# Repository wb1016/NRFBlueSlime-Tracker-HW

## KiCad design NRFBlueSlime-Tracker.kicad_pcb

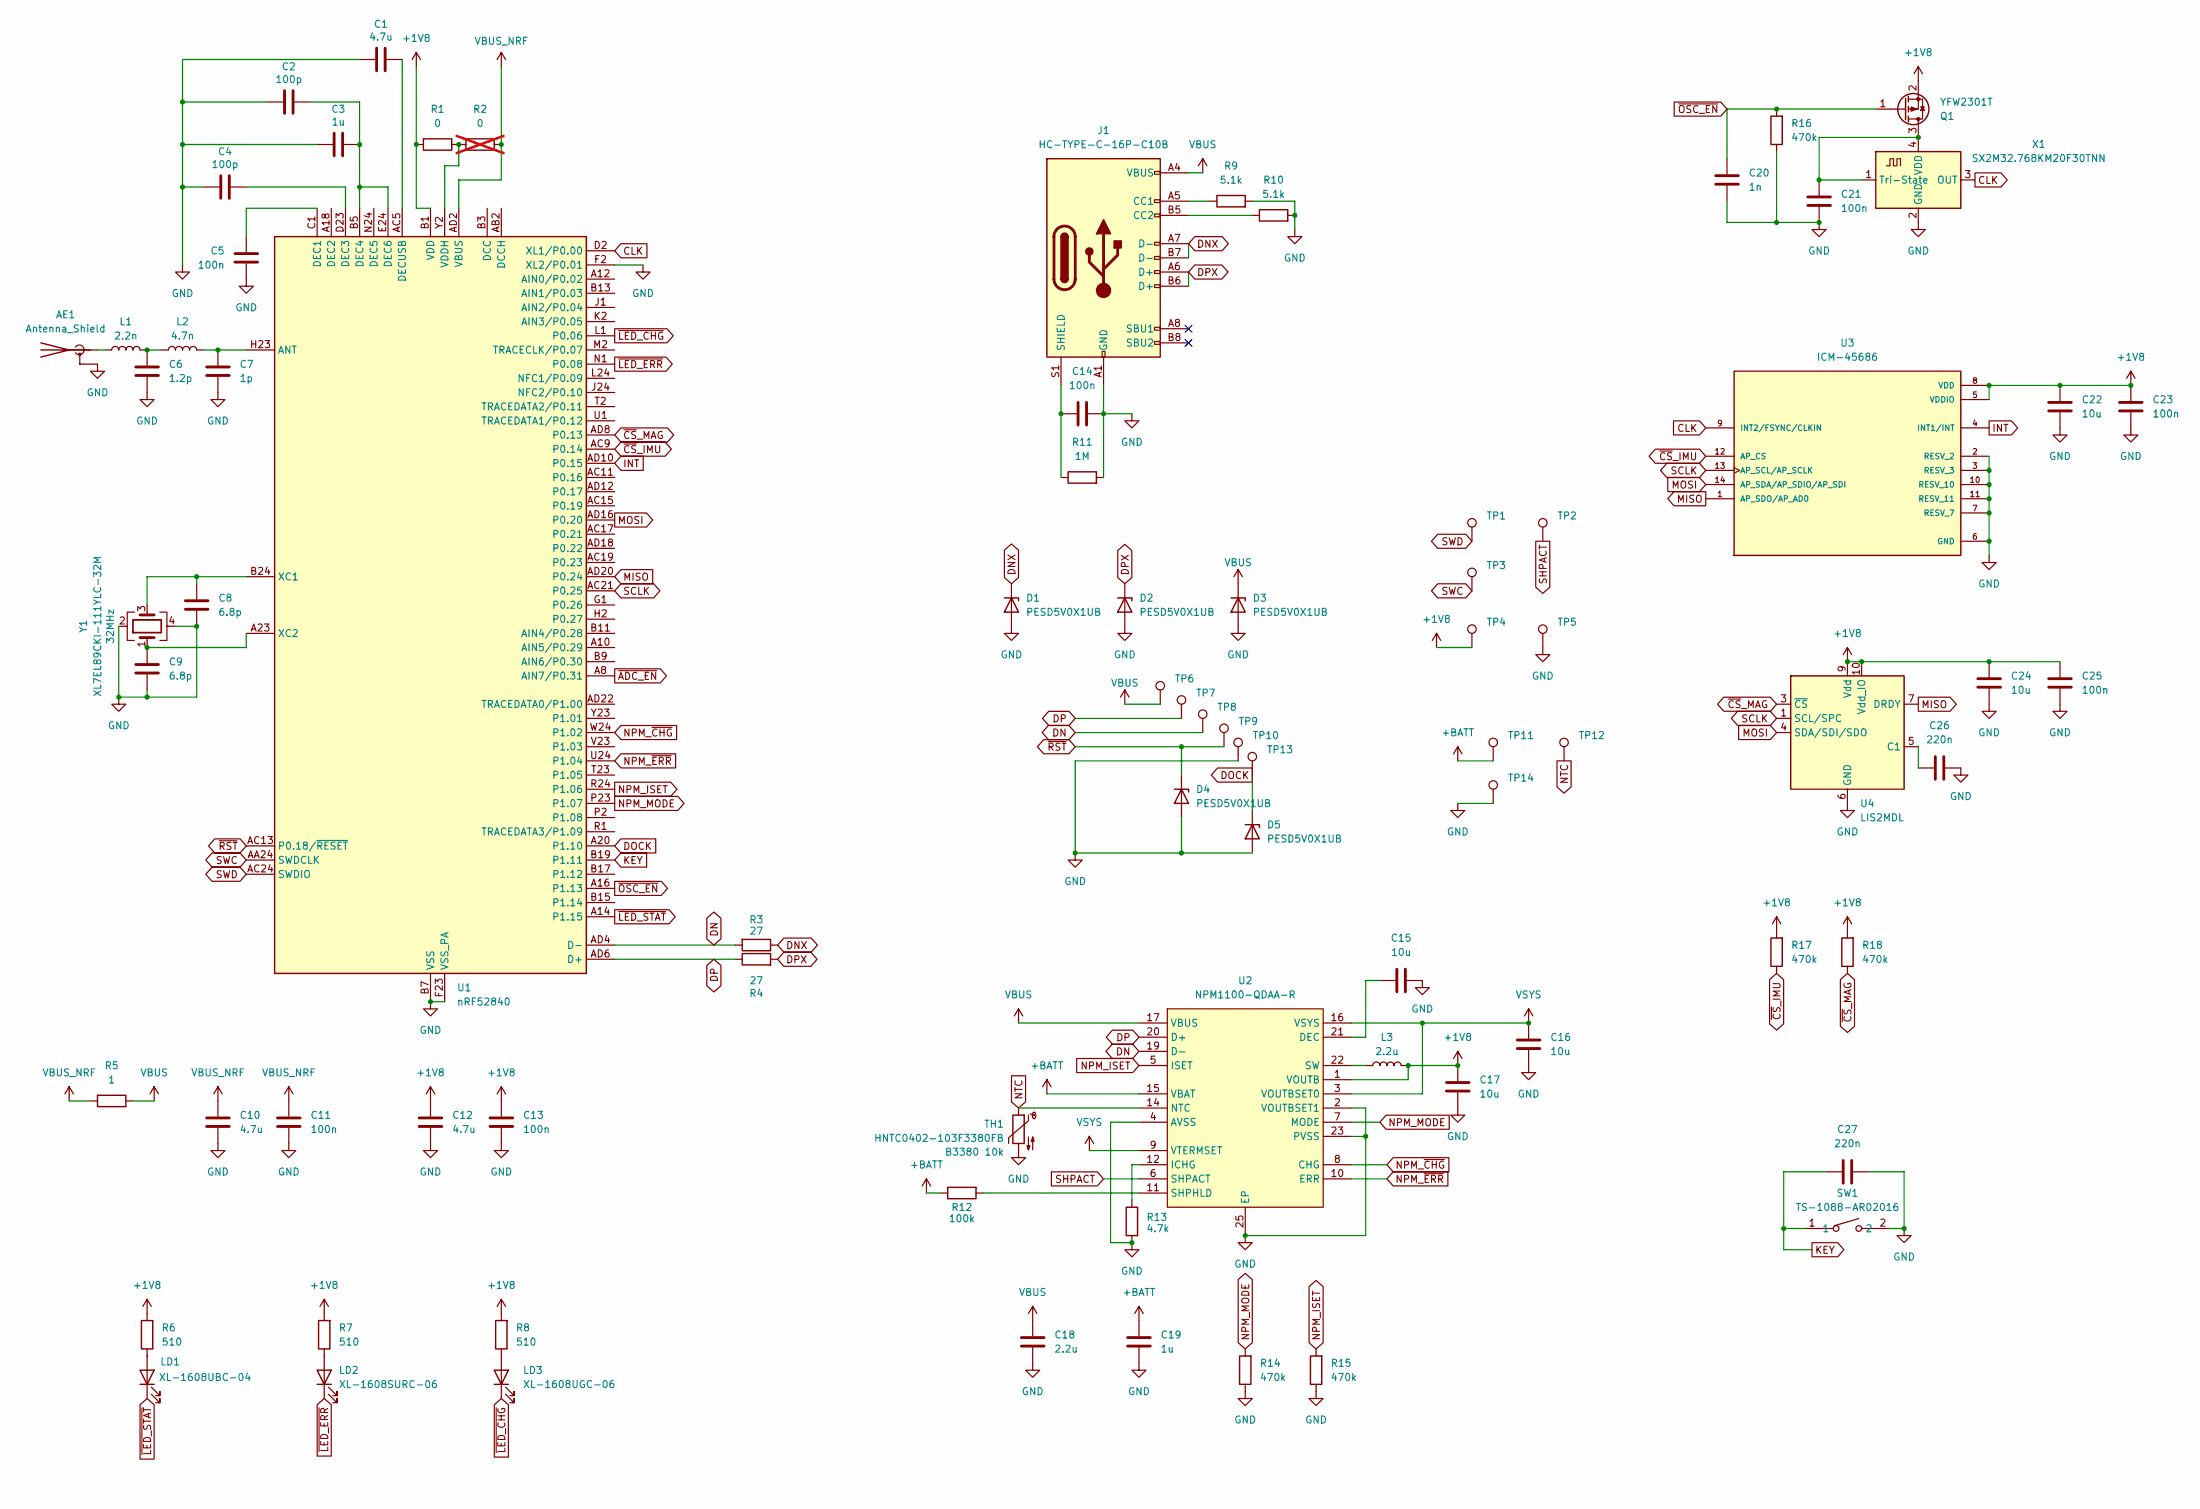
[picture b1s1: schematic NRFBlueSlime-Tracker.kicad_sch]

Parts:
AE1: Antenna_Shield; MIFA_BLE_ANT
C1, C10, C12: 4.7u; C_0603_1608Metric
C2, C4: 100p; C_0402_1005Metric
C3, C19: 1u; C_0603_1608Metric
C5, C11, C13, C14, C21, C23, C25: 100n; C_0402_1005Metric
C6: 1.2p; C_0402_1005Metric
C7: 1p; C_0402_1005Metric
C8, C9: 6.8p; C_0402_1005Metric
C15, C16, C17, C22, C24: 10u; C_0603_1608Metric
C18: 2.2u; C_0603_1608Metric
C20: 1n; C_0402_1005Metric
C26, C27: 220n; C_0402_1005Metric
D1, D2, D3, D4, D5: PESD5V0X1UB; D_SOD-882
J1: HC-TYPE-C-16P-C10B; USB-C-SMD_HC-TYPE-C-16P-C10B
L1: 2.2n; L_0402_1005Metric
L2: 4.7n; L_0402_1005Metric
L3: 2.2u; L_1210_3225Metric
LD1: XL-1608UBC-04; LED_0603_1608Metric
LD2: XL-1608SURC-06; LED_0603_1608Metric
LD3: XL-1608UGC-06; LED_0603_1608Metric
Q1: YFW2301T; SOT-523
R1: 0; R_0603_1608Metric
R2: 0; R_0603_1608Metric; not fitted
R3, R4: 27; R_0402_1005Metric
R5: 1; R_0603_1608Metric
R6, R7, R8: 510; R_0402_1005Metric
R9, R10: 5.1k; R_0402_1005Metric
R11: 1M; R_0402_1005Metric
R12: 100k; R_0402_1005Metric
R13: 4.7k; R_0402_1005Metric
R14, R15, R16, R17, R18: 470k; R_0402_1005Metric
SW1: TS-1088-AR02016; SW-SMD_L3.9-W3.0-P4.45; LCSC Part C720477
TH1: HNTC0402-103F3380FB; R_0402_1005Metric
TP1, TP2, TP3, TP4, TP5, TP6, TP7, TP8, TP9, TP10, TP11, TP12, TP13, TP14: TestPoint; TestPoint_Pad_1.0x1.0mm
U1: nRF52840; Nordic_AQFN-73-1EP_7x7mm_P0.5mm
U2: NPM1100-QDAA-R; QFN50P400X400X90-25N-D; Mouser Part Number 949-NPM1100-QDAA-R
U3: ICM-45686; PQFN50P300X250X97-14N; PARTREV 1.2
U4: LIS2MDL; LGA-12_2x2mm_P0.5mm
X1: SX2M32.768KM20F30TNN; Crystal_SMD_2520-4Pin_2.5x2.0mm; LCSC Part C387463
Y1: XL7EL89CKI-111YLC-32M; Crystal_SMD_2016-4Pin_2.0x1.6mm

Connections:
+1V8: C12.1, C13.1, C17.1, C22.1, C23.1, C24.1, C25.1, L3.2, Q1.2 (S), R1.2, R6.2, R7.2, R8.2, R17.2, R18.2, TP4.1, U1.A22 (VDD), U1.AD14 (VDD), U1.AD23 (VDD), U1.B1 (VDD), U1.W1 (VDD), U2.1 (VOUTB), U3.5 (VDDIO), U3.8 (VDD), U4.9 (Vdd), U4.10 (Vdd_IO)
+BATT: C19.2, R12.1, TP11.1, U2.15 (VBAT)
CLK: U1.D2 (XL1/P0.00), U3.9 (INT2/FSYNC/CLKIN), X1.3 (OUT)
DN: R3.2, TP8.1, U1.AD4 (D-), U2.19 (D-)
DNX: D1.1 (K), J1.A7 (D-), J1.B7 (D-), R3.1
DOCK: D5.1 (K), TP13.1, U1.A20 (P1.10)
DP: R4.1, TP7.1, U1.AD6 (D+), U2.20 (D+)
DPX: D2.1 (K), J1.A6 (D+), J1.B6 (D+), R4.2
GND: AE1.2 (Shield), C1.1, C2.1, C3.1, C4.1, C5.1, C6.1, C7.1, C8.1, C9.1, C10.2, C11.2, C12.2, C13.2, C14.2, C15.1, C16.1, C17.2, C18.1, C19.1, C20.2, C21.2, C22.2, C23.2, C24.2, C25.2, C26.2, C27.2, D1.2 (A), D2.2 (A), D3.2 (A), D4.2 (A), D5.2 (A), J1.A1 (GND), J1.A12 (GND), J1.B1 (GND), J1.B12 (GND), R9.2, R10.2, R11.2, R13.2, R14.1, R15.1, R16.1, SW1.2, TH1.2, TP5.1, TP10.1, TP14.1, U1.B7 (VSS), U1.EP (VSS), U1.F2 (XL2/P0.01), U1.F23 (VSS_PA), U2.2 (VOUTBSET1), U2.4 (AVSS), U2.23 (PVSS), U2.25 (EP), U3.2 (RESV_2), U3.3 (RESV_3), U3.6 (GND), U3.7 (RESV_7), U3.10 (RESV_10), U3.11 (RESV_11), U4.6 (GND), U4.8 (GND), X1.2 (GND), Y1.2, Y1.4
INT: U1.AD10 (P0.15), U3.4 (INT1/INT)
KEY: C27.1, SW1.1, U1.B19 (P1.11)
MISO: U1.AD20 (P0.24), U3.1 (AP_SDO/AP_AD0), U4.7 (DRDY)
MOSI: U1.AD16 (P0.20), U3.14 (AP_SDA/AP_SDIO/AP_SDI), U4.4 (SDA/SDI/SDO)
NPM_ISET: R15.2, U1.R24 (P1.06), U2.5 (ISET)
NPM_MODE: R14.2, U1.P23 (P1.07), U2.7 (MODE)
NPM_~CHG: U1.W24 (P1.02), U2.8 (CHG)
NPM_~ERR: U1.U24 (P1.04), U2.10 (ERR)
NTC: TH1.1, TP12.1, U2.14 (NTC)
unnamed: AE1.1 (A), L1.1
unnamed: C6.2, L1.2, L2.1
unnamed: J1.A5 (CC1), R9.1
unnamed: J1.B5 (CC2), R10.1
unnamed: C14.1, J1.S1 (SHIELD), R11.1
unnamed: LD1.2 (A), R6.1
unnamed: LD2.2 (A), R7.1
unnamed: LD3.2 (A), R8.1
unnamed: C21.1, Q1.3 (D), X1.1 (Tri-State), X1.4 (VDD)
unnamed: C7.2, L2.2, U1.H23 (ANT)
unnamed: C5.2, U1.C1 (DEC1)
unnamed: C4.2, U1.D23 (DEC3)
unnamed: C2.2, C3.2, U1.B5 (DEC4), U1.E24 (DEC6)
unnamed: C1.2, U1.AC5 (DECUSB)
unnamed: R1.1, R2.2, U1.Y2 (VDDH)
unnamed: C8.2, U1.B24 (XC1), Y1.3
unnamed: C9.2, U1.A23 (XC2), Y1.1
unnamed: C15.2, U2.21 (DEC)
unnamed: R13.1, U2.12 (ICHG)
unnamed: R12.2, U2.11 (SHPHLD)
unnamed: L3.1, U2.22 (SW)
unnamed: C26.1, U4.5 (C1)
SCLK: U1.AC21 (P0.25), U3.13 (AP_SCL/AP_SCLK), U4.1 (SCL/SPC)
SHPACT: TP2.1, U2.6 (SHPACT)
SWC: TP3.1, U1.AA24 (SWDCLK)
SWD: TP1.1, U1.AC24 (SWDIO)
VBUS: C18.2, D3.1 (K), J1.A4 (VBUS), J1.A9 (VBUS), J1.B4 (VBUS), J1.B9 (VBUS), R5.1, TP6.1, U2.17 (VBUS)
VBUS_NRF: C10.1, C11.1, R2.1, R5.2, U1.AD2 (VBUS)
VSYS: C16.2, U2.3 (VOUTBSET0), U2.9 (VTERMSET), U2.16 (VSYS)
~ADC_EN: U1.A8 (AIN7/P0.31)
~CS_IMU: R17.1, U1.AC9 (P0.14), U3.12 (AP_CS)
~CS_MAG: R18.1, U1.AD8 (P0.13), U4.3 (~CS)
~LED_CHG: LD3.1 (K), U1.L1 (P0.06)
~LED_ERR: LD2.1 (K), U1.N1 (P0.08)
~LED_STAT: LD1.1 (K), U1.A14 (P1.15)
~OSC_EN: C20.1, Q1.1 (G), R16.2, U1.A16 (P1.13)
~RST: D4.1 (K), TP9.1, U1.AC13 (P0.18/~RESET)

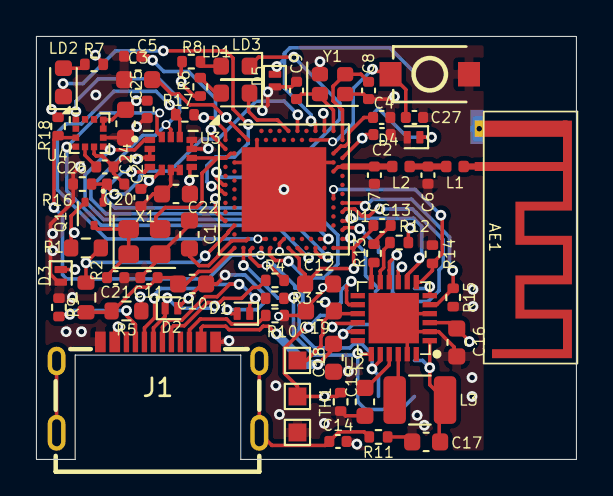
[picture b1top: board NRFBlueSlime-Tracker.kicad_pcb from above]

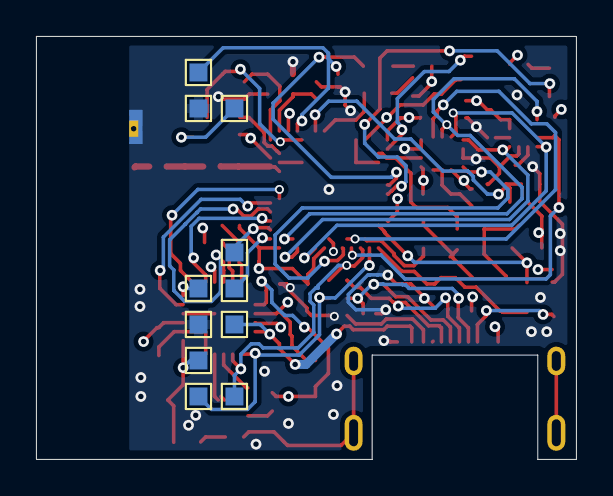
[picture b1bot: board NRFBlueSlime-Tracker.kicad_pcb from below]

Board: 4 copper layers, 30.0 x 23.5 mm, 81 parts (11 on the bottom side), 54 nets.

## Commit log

2024-04-18 asdfadsfda
2024-04-26 dhshdfsdgjfhfghj
2024-06-04 asdfa
2024-07-02 nrf52832 rev
2024-07-03 use metric spacing for dock, route switch
2024-07-28 mdbt42
2024-09-11 done nrf52840 ver
2024-09-12 hide ref, draw dimension mark
2024-09-12 fix offset sw1, upload 3d
2024-09-12 fix gnd testpad
2024-09-12 add case
2024-09-12 use copper fill in in1cu layer
2024-09-12 Label TP
2024-10-05 new ver
2025-07-24 redo schematic
2025-07-24 redo pcb
2026-01-06 sihashkdasfhjkads
2026-01-15 afdadsffas
2026-01-16 rework LEDs
2026-01-21 complete nPM
2026-01-29 do usb dual mode
2026-01-30 done sch
2026-01-30 fix mosfet upside down
2026-01-30 place components
2026-03-11 sync
2026-03-18 done pcb
